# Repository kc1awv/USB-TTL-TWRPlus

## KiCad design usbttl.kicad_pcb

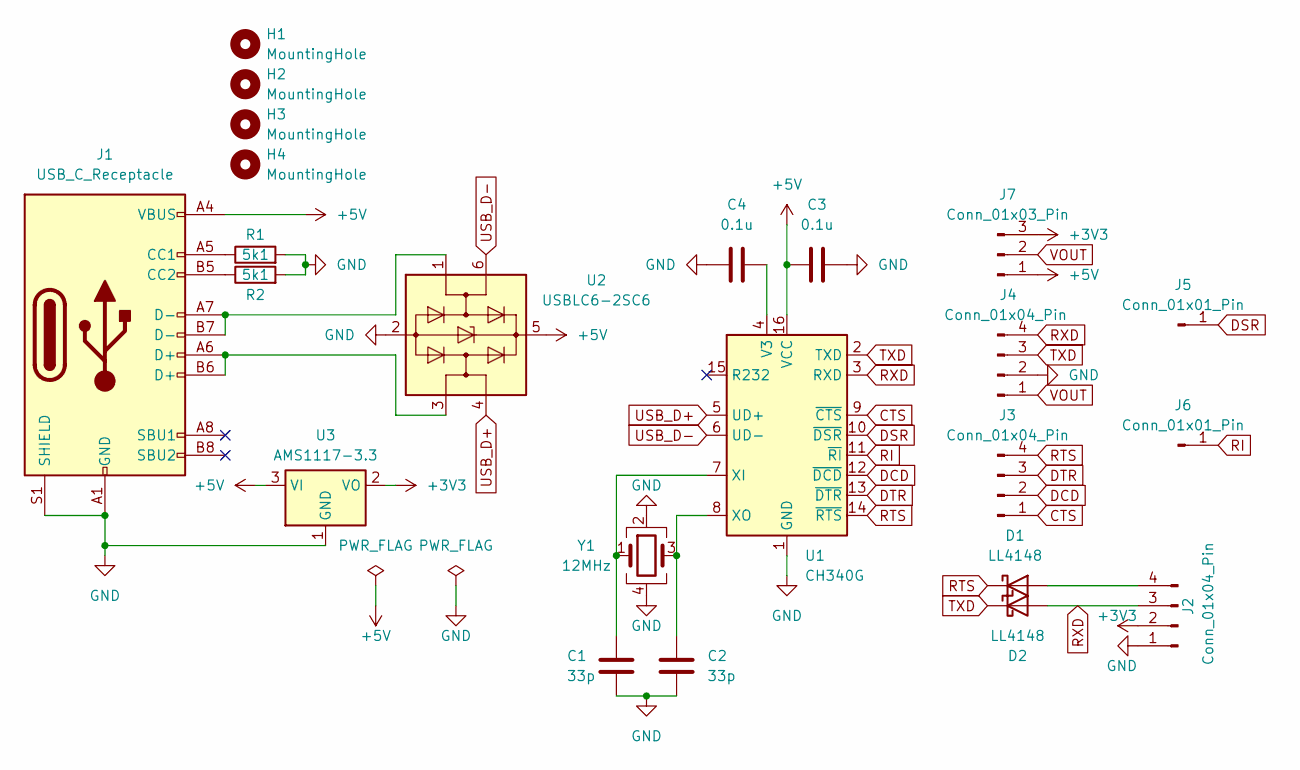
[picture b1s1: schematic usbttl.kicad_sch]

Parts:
C1, C2: 33p; C_0603_1608Metric; LCSC Part C107047
C3, C4: 0.1u; C_0603_1608Metric; LCSC Part C42998
D1, D2: LL4148; D_MiniMELF; LCSC Part C2891733
H1, H2, H3, H4: MountingHole; MountingHole_3.2mm_M3
J1: USB_C_Receptacle; USB_C_Receptacle_G-Switch_GT-USB-7010ASV; LCSC Part C2988369
J2, J3, J4: Conn_01x04_Pin; PinHeader_1x04_P2.54mm_Vertical
J5, J6: Conn_01x01_Pin; PinHeader_1x01_P2.54mm_Vertical
J7: Conn_01x03_Pin; PinHeader_1x03_P2.54mm_Vertical
R1, R2: 5k1; R_0603_1608Metric; LCSC Part C122969
U1: CH340G; SOIC-16_3.9x9.9mm_P1.27mm; LCSC Part C14267
U2: USBLC6-2SC6; SOT-23-6; LCSC Part C2827693
U3: AMS1117-3.3; SOT-223-3_TabPin2; LCSC Part C6186
Y1: 12MHz; Crystal_SMD_3225-4Pin_3.2x2.5mm; LCSC Part C9002

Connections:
+3V3: J2.2, J7.3, U3.2 (VO)
+5V: C3.1, J1.A4 (VBUS), J1.A9 (VBUS), J1.B4 (VBUS), J1.B9 (VBUS), J7.1, U1.16 (VCC), U2.5 (VBUS), U3.3 (VI)
CTS: J3.1, U1.9 (~CTS)
DCD: J3.2, U1.12 (~DCD)
DSR: J5.1, U1.10 (~DSR)
DTR: J3.3, U1.13 (~DTR)
GND: C1.2, C2.2, C3.2, C4.2, J1.A1 (GND), J1.A12 (GND), J1.B1 (GND), J1.B12 (GND), J1.S1 (SHIELD), J2.1, J4.2, R1.2, R2.2, U1.1 (GND), U2.2 (GND), U3.1 (GND), Y1.2, Y1.4
unnamed: D1.2 (A), J2.4
unnamed: J1.A5 (CC1), R1.1
unnamed: J1.B5 (CC2), R2.1
unnamed: J1.A6 (D+), J1.B6 (D+), U2.3 (I/O2)
unnamed: J1.A7 (D-), J1.B7 (D-), U2.1 (I/O1)
unnamed: C4.1, U1.4 (V3)
unnamed: C1.1, U1.7 (XI), Y1.1
unnamed: C2.1, U1.8 (XO), Y1.3
RI: J6.1, U1.11 (~RI)
RTS: D1.1 (K), J3.4, U1.14 (~RTS)
RXD: D2.2 (A), J2.3, J4.4, U1.3 (RXD)
TXD: D2.1 (K), J4.3, U1.2 (TXD)
USB_D+: U1.5 (UD+), U2.4 (I/O2)
USB_D-: U1.6 (UD-), U2.6 (I/O1)
VOUT: J4.1, J7.2

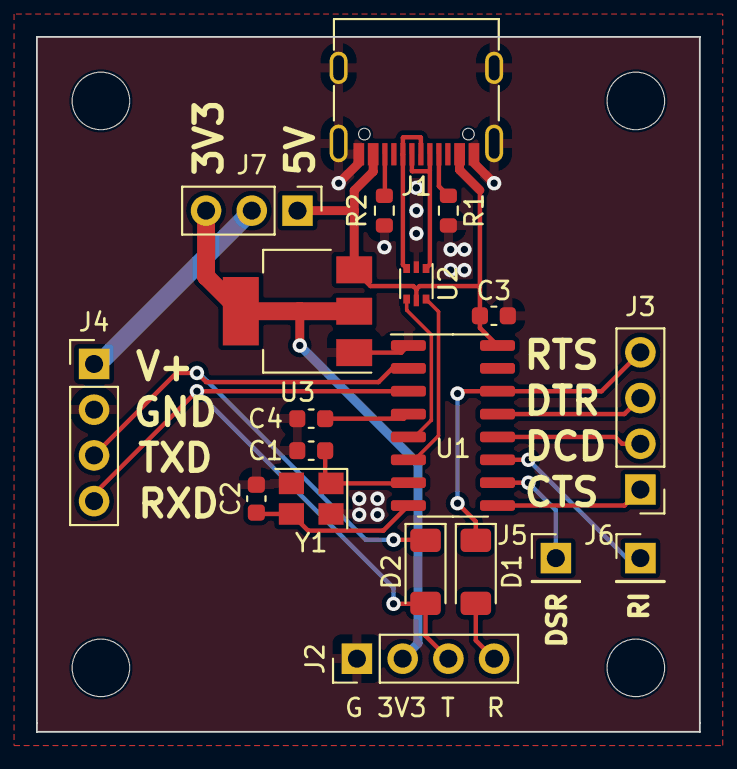
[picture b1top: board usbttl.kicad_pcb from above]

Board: 2 copper layers, 36.8 x 38.6 mm, 23 parts (0 on the bottom side), 22 nets.

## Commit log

2023-07-10 commit project
    commit project files
2023-07-10 ignore backups folder
2023-07-10 Fix DRC errors
2023-07-10 BOM and update parts
2023-07-10 position file
2023-07-10 reorganize files
2023-07-11 start rev b
